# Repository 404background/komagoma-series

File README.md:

# komagoma-series
https://404background.com/made/komagoma/

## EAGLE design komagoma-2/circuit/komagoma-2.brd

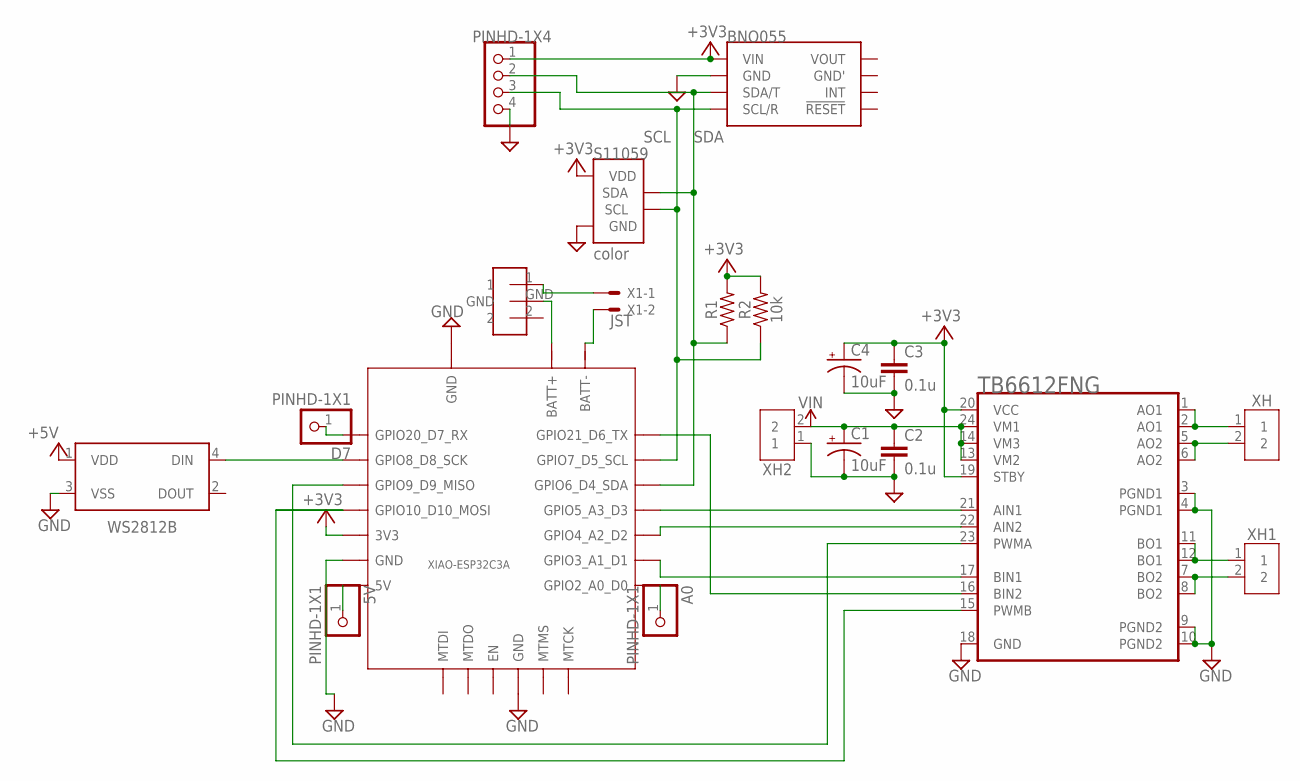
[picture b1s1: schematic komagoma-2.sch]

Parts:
5V: PINHD-1X1; 1X01
A0: PINHD-1X1; 1X01
C1, C4: 10uF; CPOL-RADIAL-2.5MM-5MM-KIT
C2, C3: 0.1u; C1608
CONNECTOR1: AKIZUKI_SWITCH_SOCKETAKIZUKI_SWITCH_SOCKET; AKIZUKI_SWITCH
D1: WS2812B
D7: PINHD-1X1; 1X01
IC1: TB6612FNGSSOP24; SOP65P760X160-24N
JP1: PINHD-1X4; 1X04
R1, R2: 10k; 0603
U1: XIAO-ESP32C3A; XIAO-ESP32C3-THRUHOLE
U$1: BNO055
U$2: S11059
X1: JST-XH-02-PIN-LONG-PAD; JST-XH-02-PACKAGE-LONG-PAD
XH, XH1, XH2: 3A/250V; B2B-XH-A

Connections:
5V: 5V.1, U1.P$14 (5V)
+3V3: C3.1, C4.1 (+), IC1.19 (STBY), IC1.20 (VCC), JP1.1, R1.2, R2.2, U1.P$12 (3V3), U$1.P$1 (VIN), U$2.P$4 (VDD)
+5V: D1.1 (VDD)
A0: A0.1, U1.P$1 (GPIO2_A0_D0)
AO1: IC1.1 (AO1), IC1.2 (AO1), XH.1
AO2: IC1.5 (AO2), IC1.6 (AO2), XH.2
BAT+: CONNECTOR1.GND, U1.22 (BATT+)
BAT-: U1.21 (BATT-), X1.2
BATT: CONNECTOR1.1, X1.1
BO1: IC1.11 (BO1), IC1.12 (BO1), XH1.1
BO2: IC1.7 (BO2), IC1.8 (BO2), XH1.2
D7: D7.1, U1.P$8 (GPIO20_D7_RX)
GND: C1.2 (-), C2.2, C3.2, C4.2 (-), D1.3 (VSS), IC1.3 (PGND1), IC1.4 (PGND1), IC1.9 (PGND2), IC1.10 (PGND2), IC1.18 (GND), JP1.4, U1.18 (GND), U1.23 (GND), U1.P$13 (GND), U$1.P$2 (GND), U$2.P$1 (GND), XH2.1
unnamed: IC1.21 (AIN1), U1.P$4 (GPIO5_A3_D3)
unnamed: IC1.22 (AIN2), U1.P$3 (GPIO4_A2_D2)
unnamed: IC1.17 (BIN1), U1.P$2 (GPIO3_A1_D1)
unnamed: IC1.16 (BIN2), U1.P$7 (GPIO21_D6_TX)
unnamed: IC1.15 (PWMB), U1.P$11 (GPIO10_D10_MOSI)
unnamed: IC1.23 (PWMA), U1.P$10 (GPIO9_D9_MISO)
unnamed: D1.4 (DIN), U1.P$9 (GPIO8_D8_SCK)
SCL: JP1.3, R2.1, U1.P$6 (GPIO7_D5_SCL), U$1.P$4 (SCL/R), U$2.P$2 (SCL)
SDA: JP1.2, R1.1, U1.P$5 (GPIO6_D4_SDA), U$1.P$3 (SDA/T), U$2.P$3 (SDA)
VM: C1.1 (+), C2.1, IC1.13 (VM2), IC1.14 (VM3), IC1.24 (VM1), XH2.2

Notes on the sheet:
TB6612FNG
JST

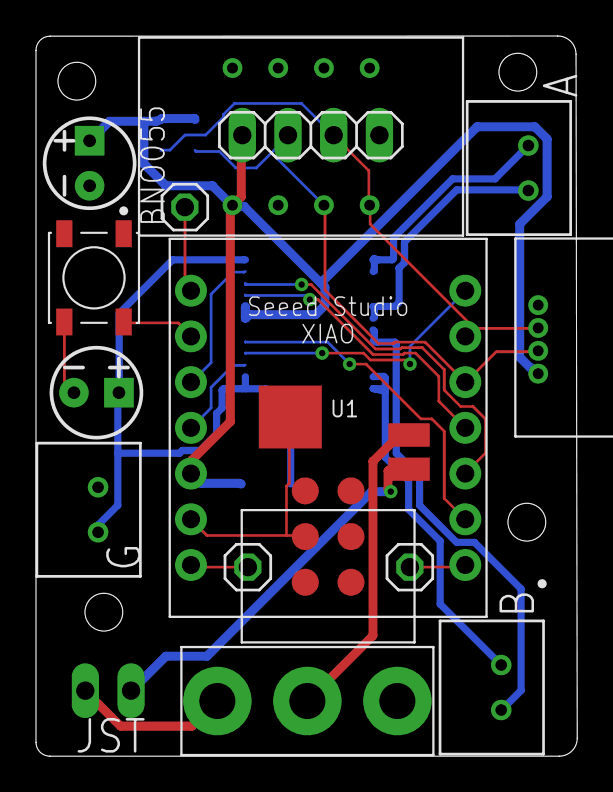
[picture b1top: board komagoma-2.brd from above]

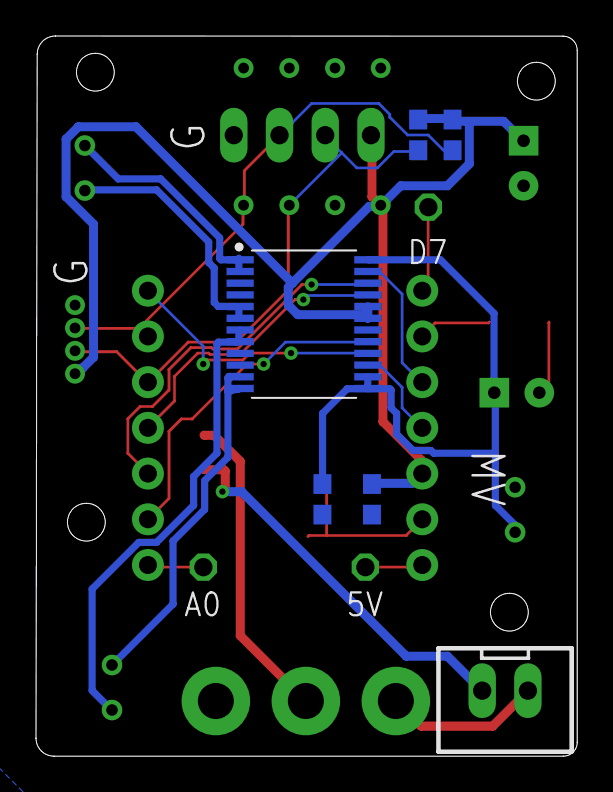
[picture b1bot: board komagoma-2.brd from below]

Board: 2 copper layers, 30.1 x 40.0 mm, 20 parts (6 on the bottom side), 22 nets.

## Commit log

2023-02-25 add:komagoma-1 .ino
2023-02-25 add:komagoma-1 picture
2023-02-25 add:komagoma-2 .sch & .brd
2023-02-25 update:komagoma-2 .brd autorouter
2023-02-27 revise : .brd & .sch
2023-02-27 order : .brd
2023-03-02 add : .ino comment
2023-03-02 move : .sch & .brd
2023-03-02 add : schematic image
2023-04-25 add : ESP32C3-iPhone
2023-04-25 move folder
2023-04-28 add : SubCore & MotorDriver
2023-04-28 update : Motor Control number
2023-12-17 add : program
2024-09-04 Add programs for komagoma-4

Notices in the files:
parts and their libraries:
SparkFun-Capacitors: Licensing: Creative Commons ShareAlike 4.0 International - https://creativecommons.org/licenses/by-sa/4.0
